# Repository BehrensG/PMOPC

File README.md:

# PMOPC
Poor man's Optical Power Converter

# Introduction
Lately, I have come across the concept of Optical Power Converters (OPC), also known as Photonic Power Converters (PPC), which supply power to circuits using light and fiber optics. This technology is interesting to me for three main reasons: voltage isolation, immunity to common-mode noise and low noise output. For more information about OPC/PPC check : [What is an Optical to Electrical Converter?](https://www.photonics.com/Articles/The-Power-of-Light-Photonic-Power-Innovations-in/a25278). Commercial OPCs can deliver up to 3 W of power. However, the main drawback is that these devices are expensive — with receiver prices starting at approximately 500 euros and transmitters costing around 1,000 euros — and they are not easy to obtain. You can only get [Broadcom](https://www.broadcom.com/products/fiber-optic-modules-components/industrial/optical-power-components) products on  Mouser or DigiKey. A cheap alternative is to use a laser diode, plastic optical fiber, and a photodiode, as described in this paper on isolated sensor networks : [Isolated sensor networks for high-voltage environments using a single polymer optical fiber and LEDs for remote powering as well as data transmission](https://jsss.copernicus.org/articles/7/193/2018/). The downside to this photodiode approach is the limited output power, which is measured only in milliwatts. To overcome these limitations, the solution I would like to test is using infrared LEDs to shine on photovoltaic cells to generate output power.

# Design
Design was done using KiCAD 10.

## LED
Two layer PCB with 8x [SFH 4715AS](https://ams-osram.com/products/leds/ir-leds/osram-oslon-black-sfh-4715as) LEDs controlled with a current source.

## OPC
Two layer PCB with 2x6 solar cell matrix using [SM111K09L](https://waf-e.dubudisk.com/anysolar.dubuplus.com/techsupport@anysolar.biz/O18Adzr/DubuDisk/www/Gen2/SM111K09L%20DATA%20SHEET%20202007.pdf).

# Implementation

I mounted only four solar cells due to the layout of the LED board design. Since each solar cell requires two LEDs and the LED board accommodates a maximum of eight LEDs, four cells is the limit. The 8 LED limits is because I want to use 24V max. 

# Measurements

Used a 34410A DMM for voltage and current measurements. Measurement done for two distance between OPC-LED : 20 mm and 40 mm.

<figure align="center">
  
  <figcaption>Figure 1: Open circuit voltage measurement. The LEDs were cooled with a fan. DMM: PLC 10, 1000 samples.</figcaption>
</figure>
<br><br>

<figure align="center">
  
  <figcaption>Figure 2: Short circuit current measurement. The LEDs were cooled with a fan. DMM: PLC 10, 1000 samples.</figcaption>
</figure>
<br><br>

<figure align="center">
  
  <figcaption>Figure 3: Voltage measurement with 110 ohm load. The LEDs were cooled with a fan. DMM: PLC 10, 1000 samples.</figcaption>
</figure>
<br><br>

<figure align="center">
  
  <figcaption>Figure 4: Current measurement with 110 ohm load. The LEDs were cooled with a fan. DMM: PLC 10, 1000 samples.</figcaption>
</figure>
<br><br>

<figure align="center">
  
  <figcaption>Figure 5: Voltage measurement with 110 ohm load. The LEDs and solar cells were cooled with a fan. DMM: PLC 10, 10000 samples. Distance 20 mm.</figcaption>
</figure>
<br><br>

<figure align="center">
  
  <figcaption>Figure 6: Current measurement with 110 ohm load. The LEDs and solar cells were cooled with a fan. DMM: PLC 10, 10000 samples. Distance 20 mm.</figcaption>
</figure>

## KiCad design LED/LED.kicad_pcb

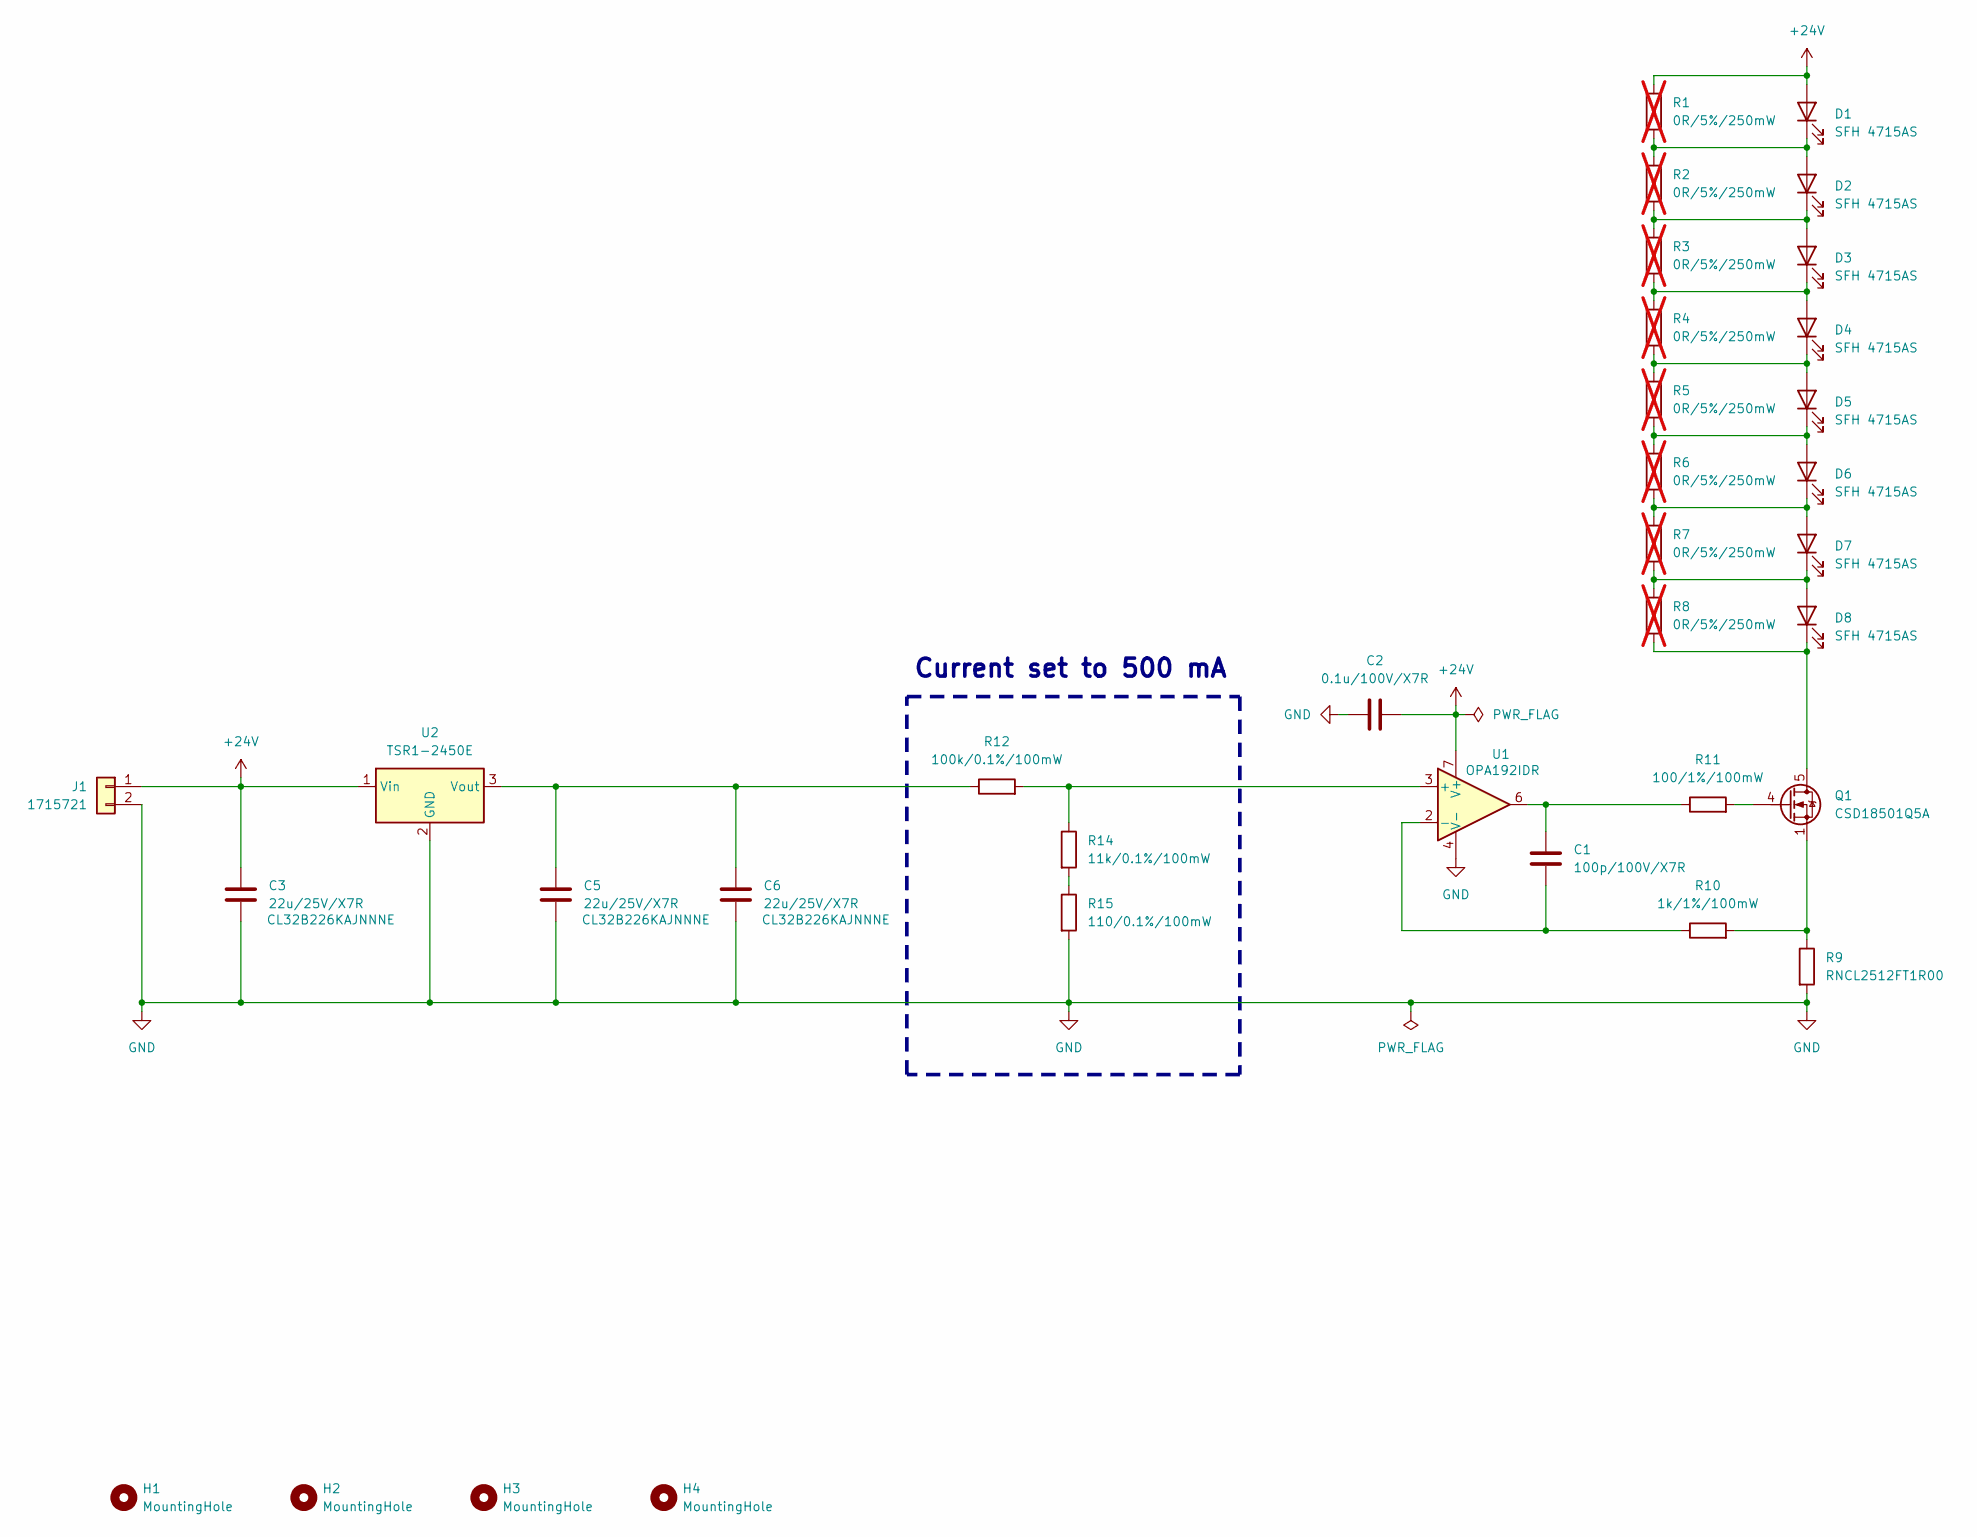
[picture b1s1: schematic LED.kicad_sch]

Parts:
C1: 100p/100V/X7R; C_0603_1608Metric_Pad1.08x0.95mm_HandSolder
C2: 0.1u/100V/X7R; C_0603_1608Metric_Pad1.08x0.95mm_HandSolder
C3, C5, C6: 22u/25V/X7R; C_1210_3225Metric_Pad1.33x2.70mm_HandSolder
D1, D2, D3, D4, D5, D6, D7, D8: SFH 4715AS; SFH4715AS
H1, H2, H3, H4: MountingHole; MountingHole_3.2mm_M3_DIN965
J1: 1715721; TerminalBlock_Phoenix_MKDS-1,5-2_1x02_P5.00mm_Horizontal
Q1: CSD18501Q5A; TDSON-8-1
R1, R2, R3, R4, R5, R6, R7, R8: 0R/5%/250mW; R_2512_6332Metric_Pad1.40x3.35mm_HandSolder; not fitted
R9: RNCL2512FT1R00; R_2512_6332Metric_Pad1.40x3.35mm_HandSolder
R10: 1k/1%/100mW; R_0603_1608Metric_Pad0.98x0.95mm_HandSolder
R11: 100/1%/100mW; R_0603_1608Metric_Pad0.98x0.95mm_HandSolder
R12: 100k/0.1%/100mW; R_0603_1608Metric_Pad0.98x0.95mm_HandSolder
R14: 11k/0.1%/100mW; R_0603_1608Metric_Pad0.98x0.95mm_HandSolder
R15: 110/0.1%/100mW; R_0603_1608Metric_Pad0.98x0.95mm_HandSolder
U1: OPA192IDR; SOIC-8_3.9x4.9mm_P1.27mm
U2: TSR1-2450E; Converter_DCDC_TRACO_TSR1-xxxxE_THT

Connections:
+24V: C2.2, C3.1, D1.2 (A), J1.1, R1.1, U1.7 (V+), U2.1 (Vin)
GND: C2.1, C3.2, C5.2, C6.2, J1.2, R9.2, R15.2, U1.4 (V-), U2.2 (GND)
unnamed: C1.1, R11.1, U1.6
unnamed: D1.1 (K), D2.2 (A), R1.2, R2.1
unnamed: D2.1 (K), D3.2 (A), R2.2, R3.1
unnamed: D3.1 (K), D4.2 (A), R3.2, R4.1
unnamed: D4.1 (K), D5.2 (A), R4.2, R5.1
unnamed: D5.1 (K), D6.2 (A), R5.2, R6.1
unnamed: D6.1 (K), D7.2 (A), R6.2, R7.1
unnamed: D7.1 (K), D8.2 (A), R7.2, R8.1
unnamed: D8.1 (K), Q1.5 (D), R8.2
unnamed: Q1.4 (G), R11.2
unnamed: Q1.1 (S), Q1.2 (S), Q1.3 (S), R9.1, R10.2
unnamed: R14.2, R15.1
unnamed: R12.2, R14.1, U1.3 (+)
unnamed: C1.2, R10.1, U1.2 (-)
unnamed: C5.1, C6.1, R12.1, U2.3 (Vout)

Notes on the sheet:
Current set to 500 mA

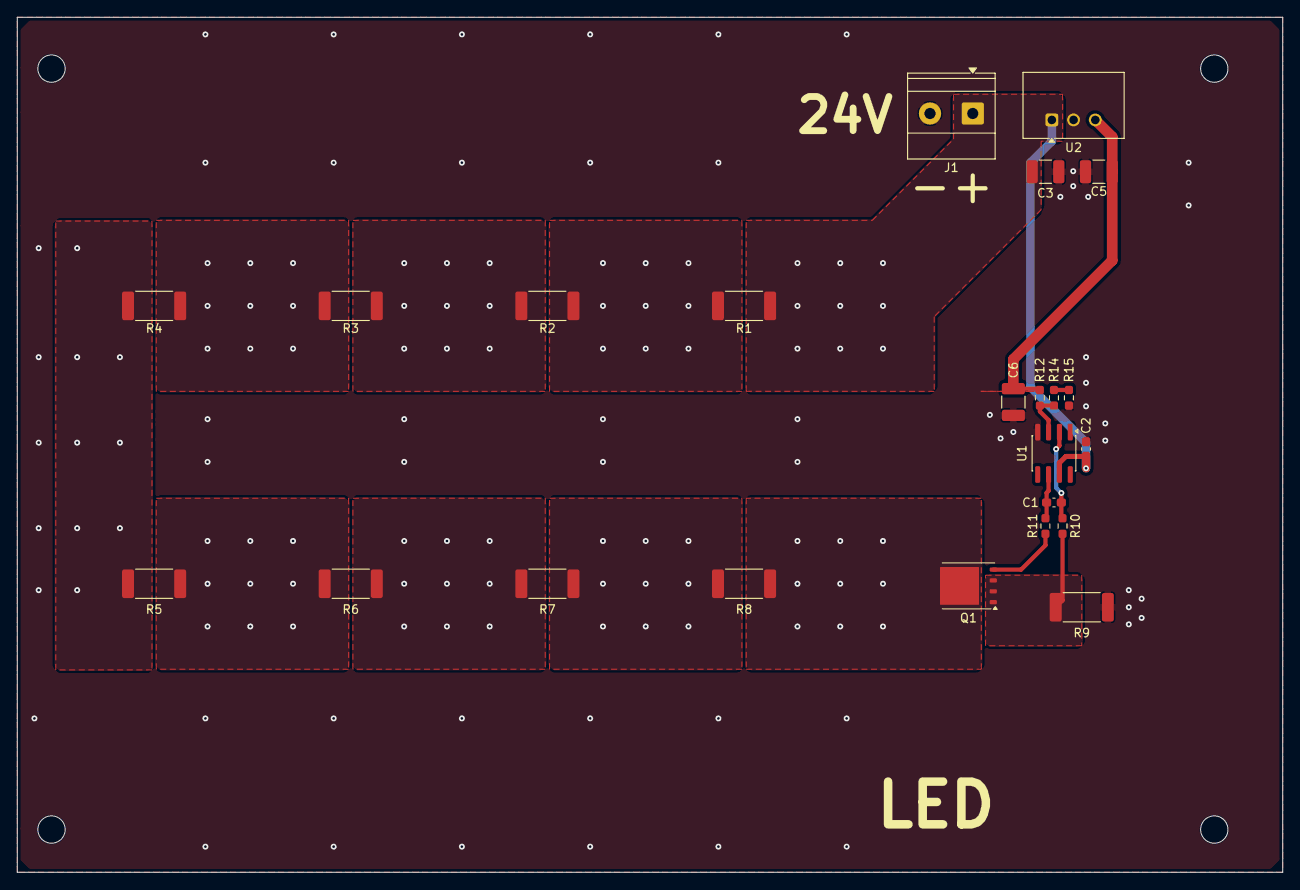
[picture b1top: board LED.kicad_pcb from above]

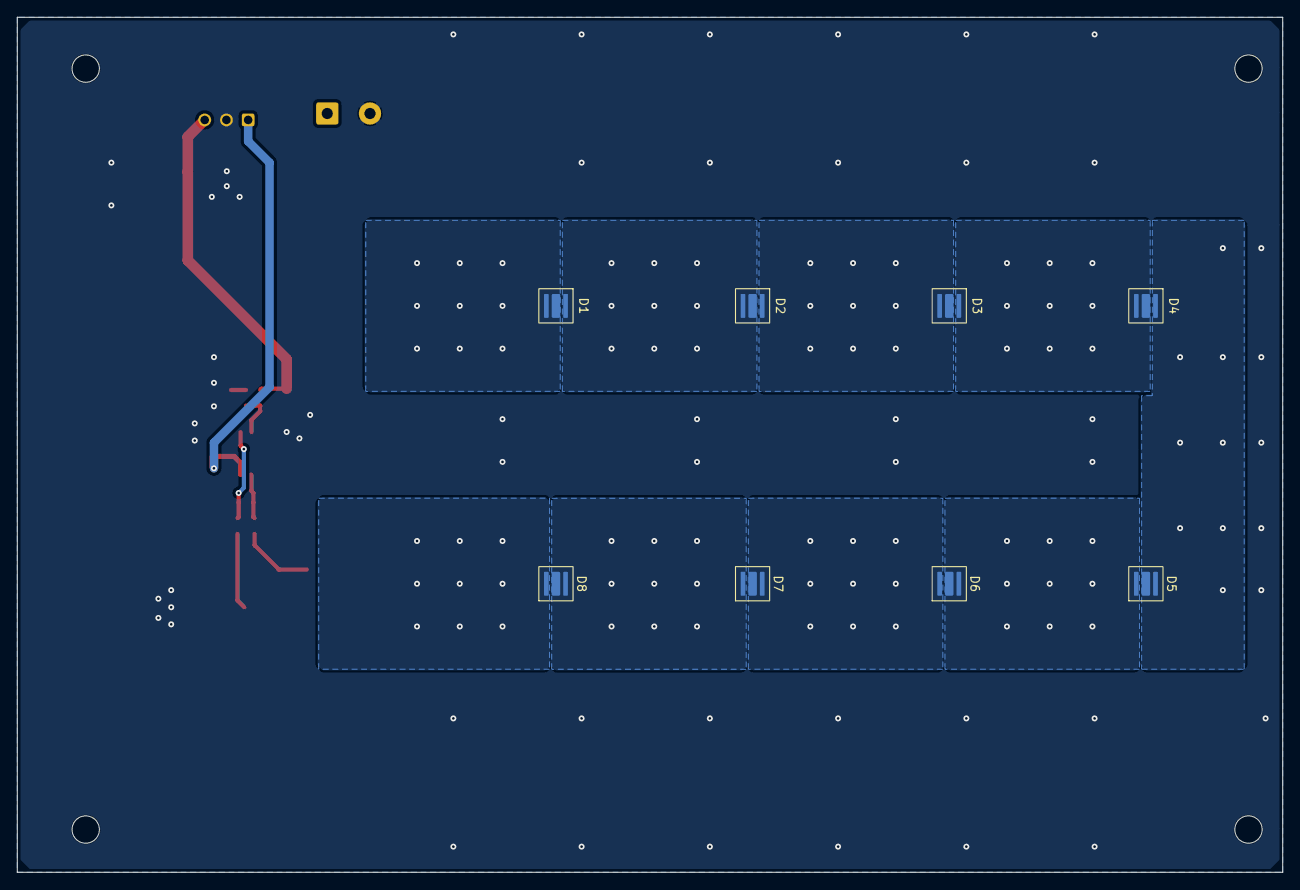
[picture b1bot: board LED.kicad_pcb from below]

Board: 2 copper layers, 148.0 x 100.0 mm, 35 parts (8 on the bottom side), 17 nets.

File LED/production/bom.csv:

Designator,Footprint,Quantity,Value,LCSC Part #
C1,0603,1,100p/100V/X7R,
C2,0603,1,0.1u/100V/X7R,
"C3, C5, C6",1210,3,22u/25V/X7R,
"D1, D2, D3, D4, D5, D6, D7, D8",SFH4715AS,8,SFH 4715AS,
J1,"TerminalBlock_Phoenix_MKDS-1,5-2_1x02_P5.00mm_Horizontal",1,1715721,
Q1,TDSON-8-1,1,CSD18501Q5A,
"R1, R2, R3, R4, R5, R6, R7, R8",2512,8,0R/5%/250mW,
R10,0603,1,1k/1%/100mW,
R11,0603,1,100/1%/100mW,
R12,0603,1,100k/0.1%/100mW,
R14,0603,1,11k/0.1%/100mW,
R15,0603,1,110/0.1%/100mW,
R9,2512,1,RNCL2512FT1R00,
U1,SOIC-8_3.9x4.9mm_P1.27mm,1,OPA192IDR,
U2,Converter_DCDC_TRACO_TSR1-xxxxE_THT,1,TSR1-2450E,

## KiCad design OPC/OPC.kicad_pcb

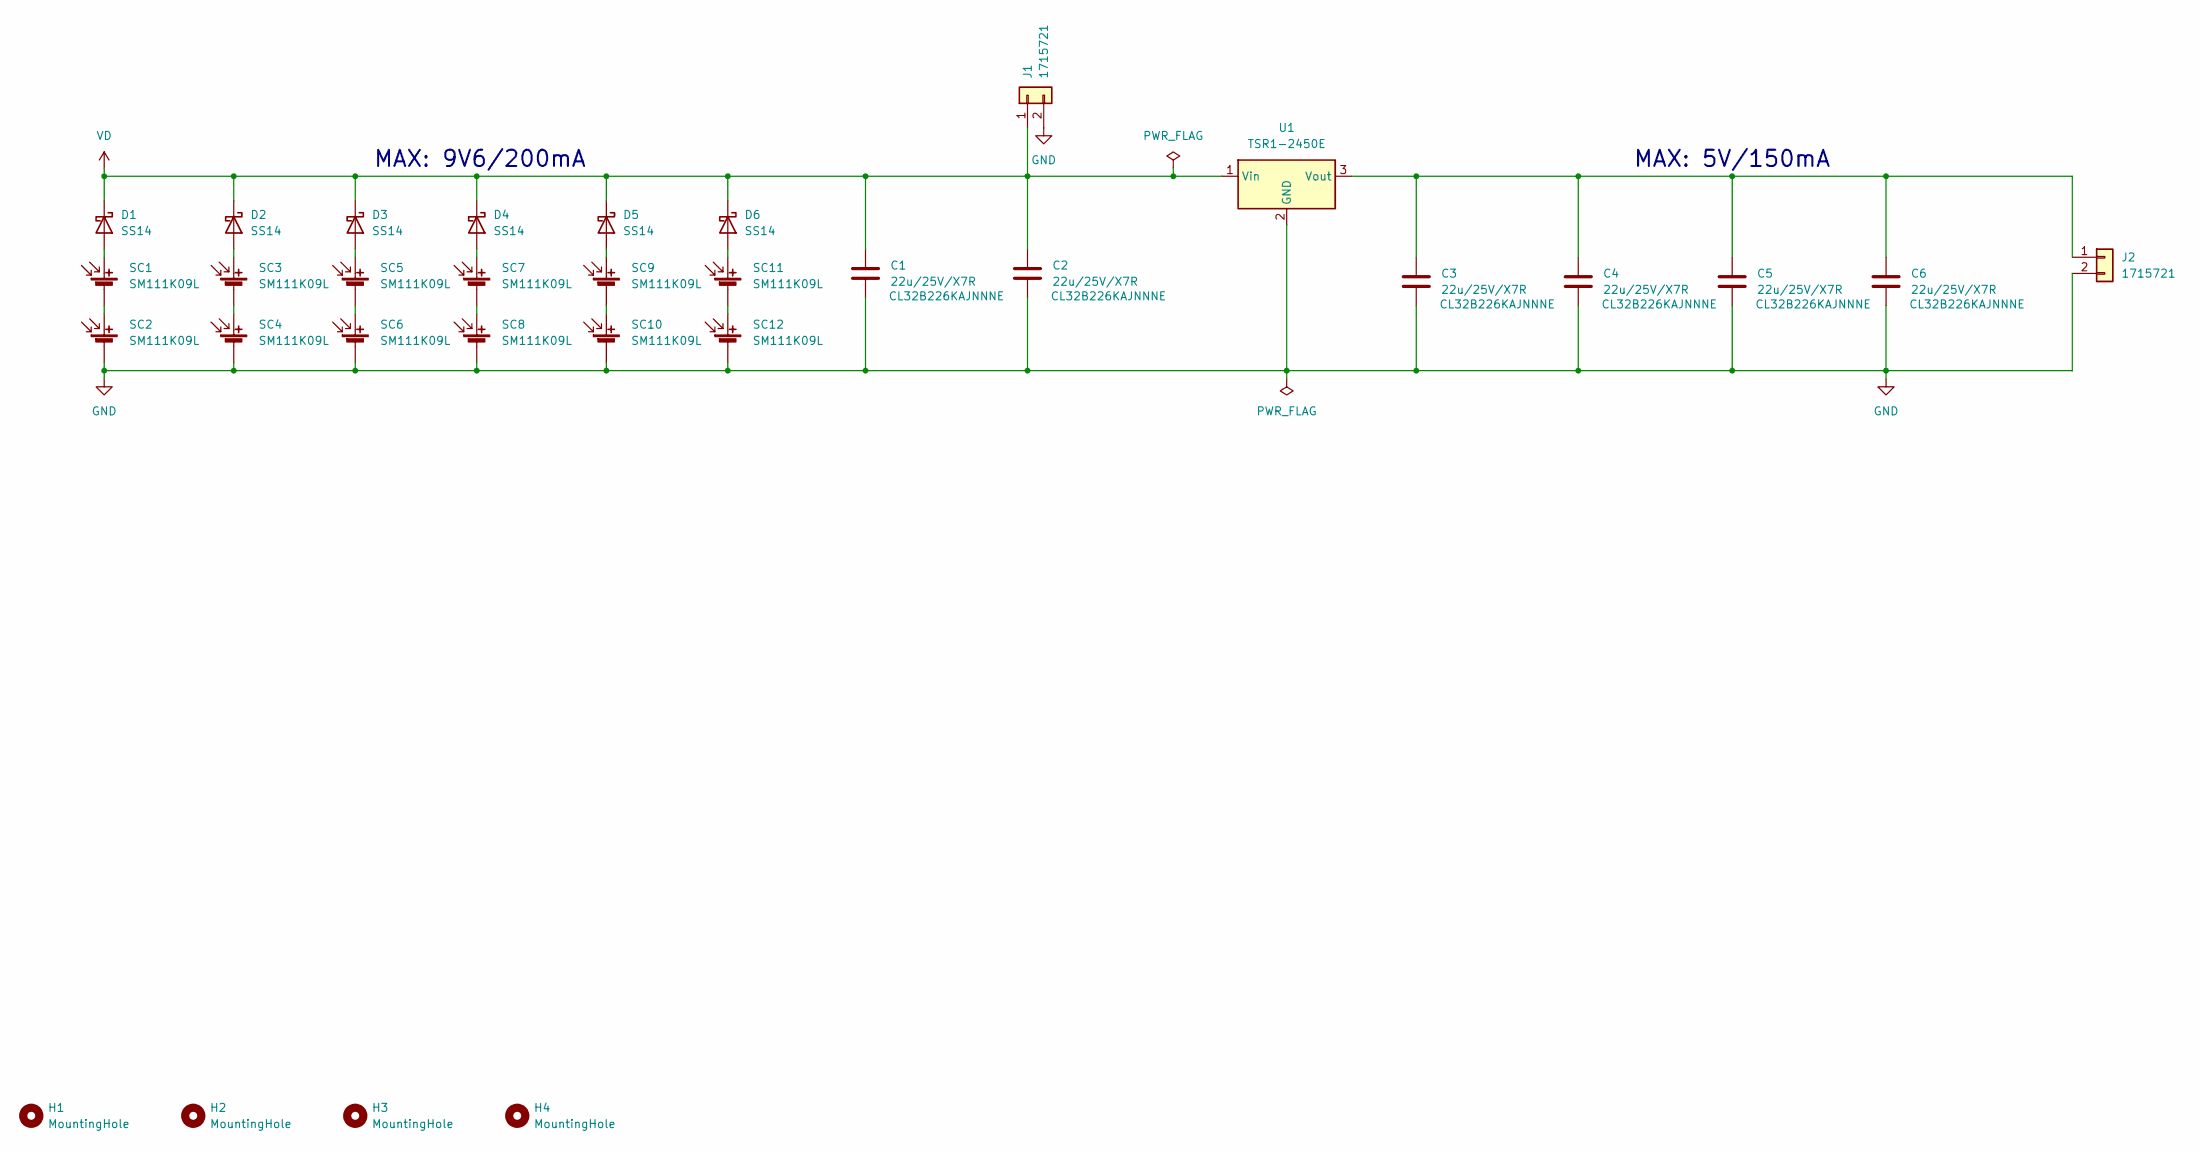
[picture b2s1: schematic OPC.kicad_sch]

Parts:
C1, C2, C3, C4, C5, C6: 22u/25V/X7R; C_1210_3225Metric_Pad1.33x2.70mm_HandSolder
D1, D2, D3, D4, D5, D6: SS14; D_SMA
H1, H2, H3, H4: MountingHole; MountingHole_3.2mm_M3_DIN965
J1, J2: 1715721; TerminalBlock_Phoenix_MKDS-1,5-2_1x02_P5.00mm_Horizontal
SC1, SC2, SC3, SC4, SC5, SC6, SC7, SC8, SC9, SC10, SC11, SC12: SM111K09L
U1: TSR1-2450E; Converter_DCDC_TRACO_TSR1-xxxxE_THT

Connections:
GND: C1.2, C2.2, C3.2, C4.2, C5.2, C6.2, J1.2, J2.2, SC2.2 (-), SC4.2 (-), SC6.2 (-), SC8.2 (-), SC10.2 (-), SC12.2 (-), U1.2 (GND)
unnamed: D1.2 (A), SC1.1 (+)
unnamed: D2.2 (A), SC3.1 (+)
unnamed: D3.2 (A), SC5.1 (+)
unnamed: D4.2 (A), SC7.1 (+)
unnamed: D5.2 (A), SC9.1 (+)
unnamed: D6.2 (A), SC11.1 (+)
unnamed: C3.1, C4.1, C5.1, C6.1, J2.1, U1.3 (Vout)
unnamed: SC1.2 (-), SC2.1 (+)
unnamed: SC3.2 (-), SC4.1 (+)
unnamed: SC5.2 (-), SC6.1 (+)
unnamed: SC7.2 (-), SC8.1 (+)
unnamed: SC9.2 (-), SC10.1 (+)
unnamed: SC11.2 (-), SC12.1 (+)
VD: C1.1, C2.1, D1.1 (K), D2.1 (K), D3.1 (K), D4.1 (K), D5.1 (K), D6.1 (K), J1.1, U1.1 (Vin)

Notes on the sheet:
MAX: 5V/150mA
MAX: 9V6/200mA

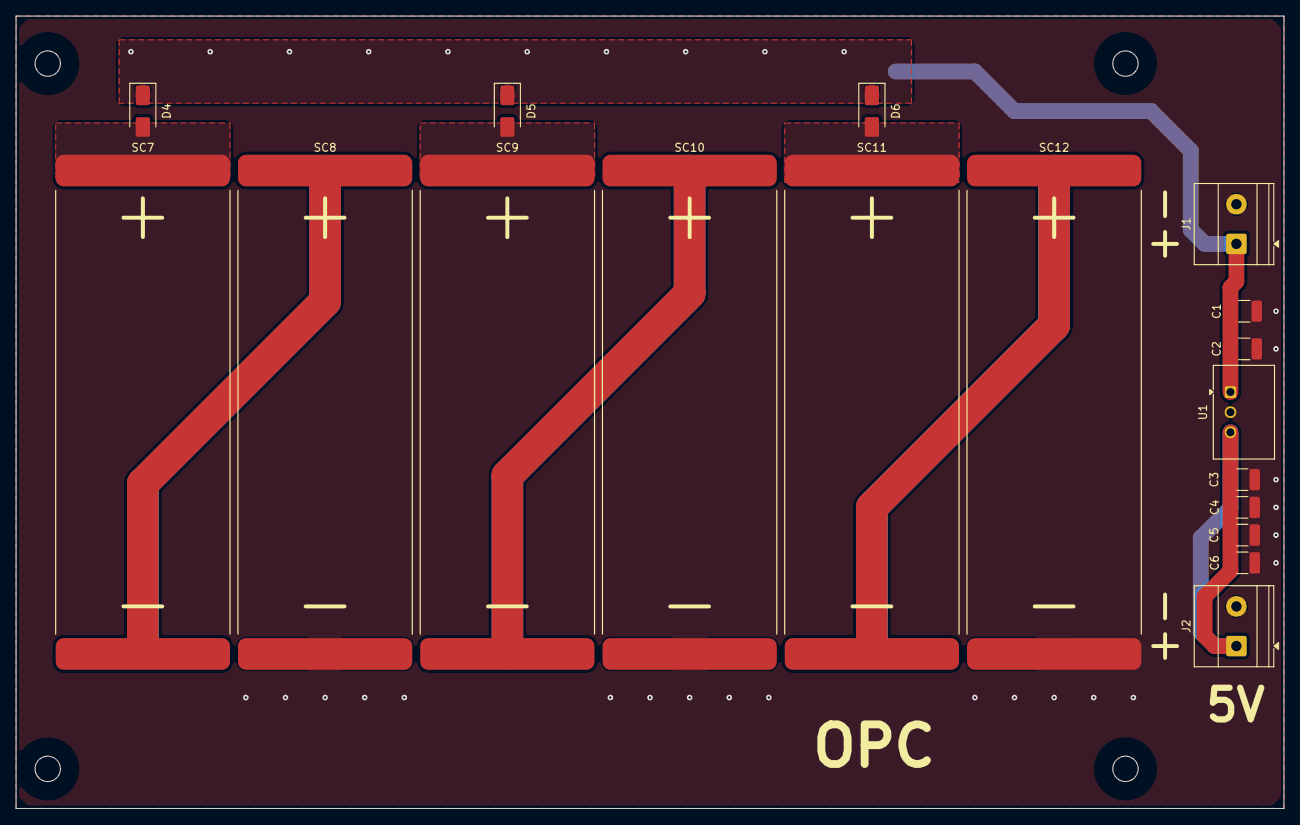
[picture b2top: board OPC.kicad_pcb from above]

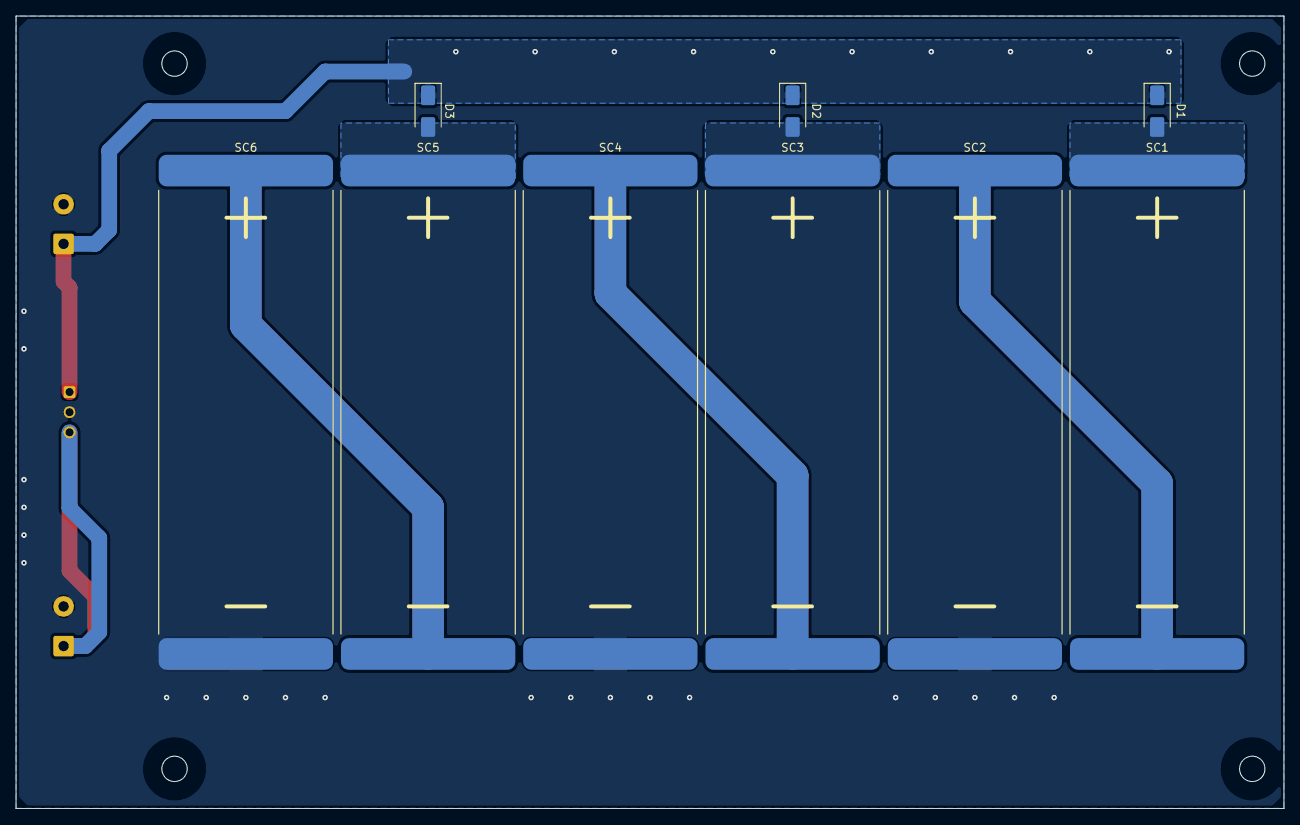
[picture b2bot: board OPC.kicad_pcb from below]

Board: 2 copper layers, 160.0 x 100.0 mm, 31 parts (9 on the bottom side), 15 nets.

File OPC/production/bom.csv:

Designator,Footprint,Quantity,Value,LCSC Part #
"C1, C2, C3, C4, C5, C6",1210,6,22u/25V/X7R,
"D1, D2, D3, D4, D5, D6",D_SMA,6,SS14,
"J1, J2","TerminalBlock_Phoenix_MKDS-1,5-2_1x02_P5.00mm_Horizontal",2,1715721,
"SC1, SC10, SC11, SC12, SC2, SC3, SC4, SC5, SC6, SC7, SC8, SC9",SM111K09L,12,SM111K09L,
U1,Converter_DCDC_TRACO_TSR1-xxxxE_THT,1,TSR1-2450E,

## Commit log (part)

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2026-06-08 Development
2026-06-13 Design done
2026-06-28 Updated README file
